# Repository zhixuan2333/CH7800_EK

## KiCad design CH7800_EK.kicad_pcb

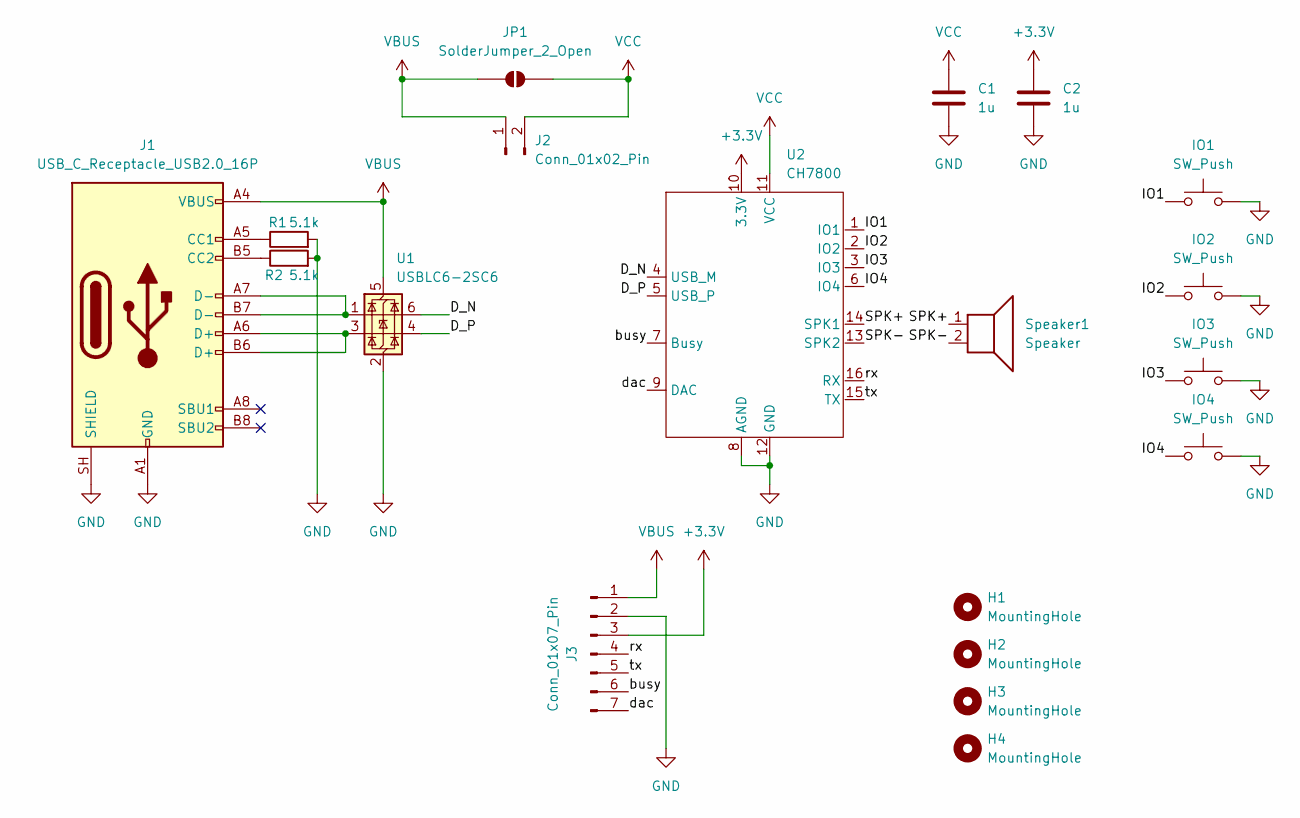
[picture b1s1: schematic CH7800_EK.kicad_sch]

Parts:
C1, C2: 1u; C_0603_1608Metric
H1, H2, H3, H4: MountingHole; MountingHole_3.2mm_M3
IO1, IO2, IO3, IO4: SW_Push; SW_PUSH_6mm
J1: USB_C_Receptacle_USB2.0_16P; USB_C_Receptacle_Palconn_UTC16-G
J2: Conn_01x02_Pin; PinHeader_1x02_P2.54mm_Vertical
J3: Conn_01x07_Pin; PinHeader_1x07_P2.54mm_Vertical
JP1: SolderJumper_2_Open; SolderJumper-2_P1.3mm_Open_RoundedPad1.0x1.5mm
R1, R2: 5.1k; R_0603_1608Metric
Speaker1: Speaker; TerminalBlock_MaiXu_MX126-5.0-02P_1x02_P5.00mm
U1: USBLC6-2SC6; SOT-23-6
U2: CH7800; SOIC-16_3.9x9.9mm_P1.27mm

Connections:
+3.3V: C2.1, J3.3, U2.10 (3.3V)
/D_N: U1.6 (I/O1), U2.4 (USB_M)
/D_P: U1.4 (I/O2), U2.5 (USB_P)
/IO1: IO1.1, U2.1 (IO1)
/IO2: IO2.1, U2.2 (IO2)
/IO3: IO3.1, U2.3 (IO3)
/IO4: IO4.1, U2.6 (IO4)
/SPK+: Speaker1.1, U2.14 (SPK1)
/SPK-: Speaker1.2, U2.13 (SPK2)
/busy: J3.6, U2.7 (Busy)
/dac: J3.7, U2.9 (DAC)
/rx: J3.4, U2.16 (RX)
/tx: J3.5, U2.15 (TX)
GND: C1.2, C2.2, IO1.2, IO2.2, IO3.2, IO4.2, J1.A1 (GND), J1.A12 (GND), J1.B1 (GND), J1.B12 (GND), J1.SH (SHIELD), J3.2, R1.2, R2.2, U1.2 (GND), U2.8 (AGND), U2.12 (GND)
unnamed: J1.A5 (CC1), R1.1
unnamed: J1.B5 (CC2), R2.1
unnamed: J1.A6 (D+), J1.B6 (D+), U1.3 (I/O2)
unnamed: J1.A7 (D-), J1.B7 (D-), U1.1 (I/O1)
VBUS: J1.A4 (VBUS), J1.A9 (VBUS), J1.B4 (VBUS), J1.B9 (VBUS), J2.1, J3.1, JP1.1 (A), U1.5 (VBUS)
VCC: C1.1, J2.2, JP1.2 (B), U2.11 (VCC)

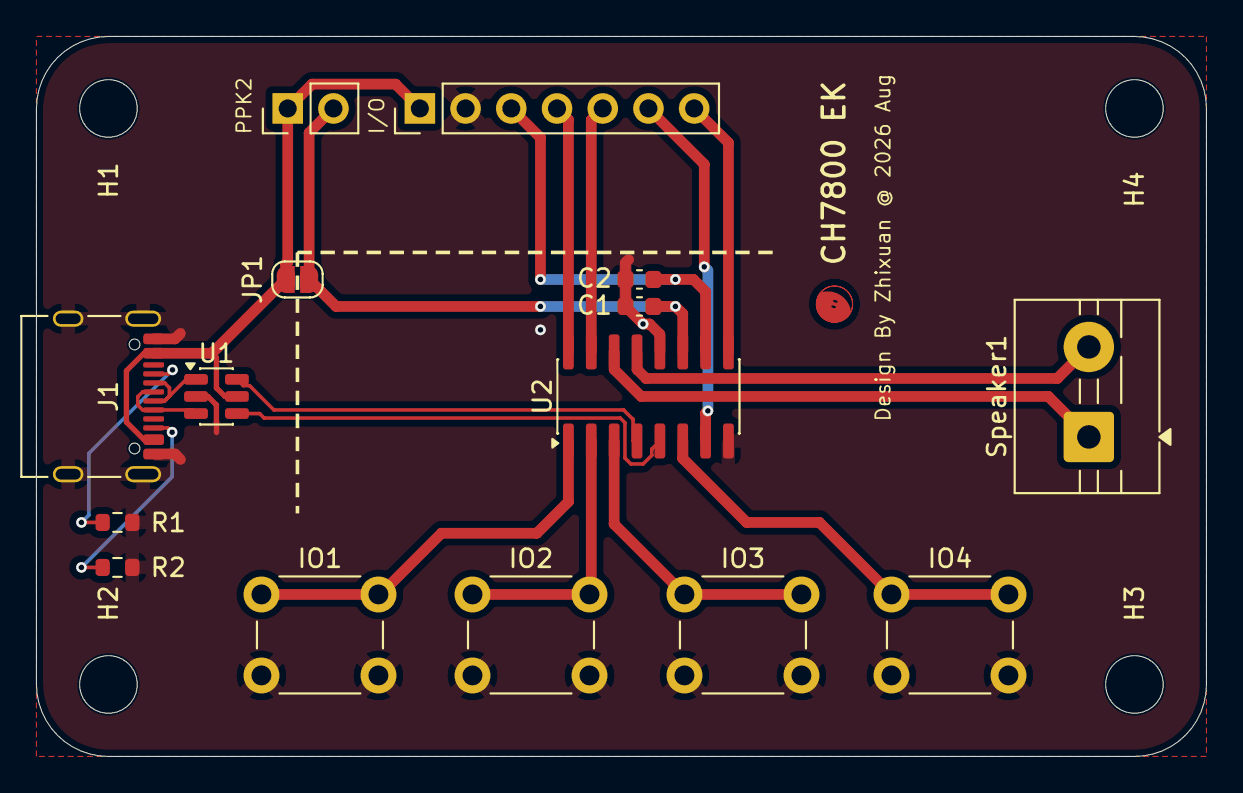
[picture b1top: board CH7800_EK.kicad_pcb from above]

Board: 2 copper layers, 65.0 x 40.0 mm, 19 parts (0 on the bottom side), 20 nets.

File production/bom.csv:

Designator,Footprint,Quantity,Value,LCSC Part #
"C1, C2",0603,2,1u,
"IO1, IO2, IO3, IO4",SW_PUSH_6mm,4,SW_Push,
J1,USB_C_Receptacle_Palconn_UTC16-G,1,USB_C_Receptacle_USB2.0_16P,
J2,PinHeader_1x02_P2.54mm_Vertical,1,Conn_01x02_Pin,
J3,PinHeader_1x07_P2.54mm_Vertical,1,Conn_01x07_Pin,
"R1, R2",0603,2,5.1k,
SPEAKER1,TerminalBlock_MaiXu_MX126-5.0-02P_1x02_P5.00mm,1,Speaker,
U1,SOT-23-6,1,USBLC6-2SC6,
U2,SOIC-16_3.9x9.9mm_P1.27mm,1,CH7800,
